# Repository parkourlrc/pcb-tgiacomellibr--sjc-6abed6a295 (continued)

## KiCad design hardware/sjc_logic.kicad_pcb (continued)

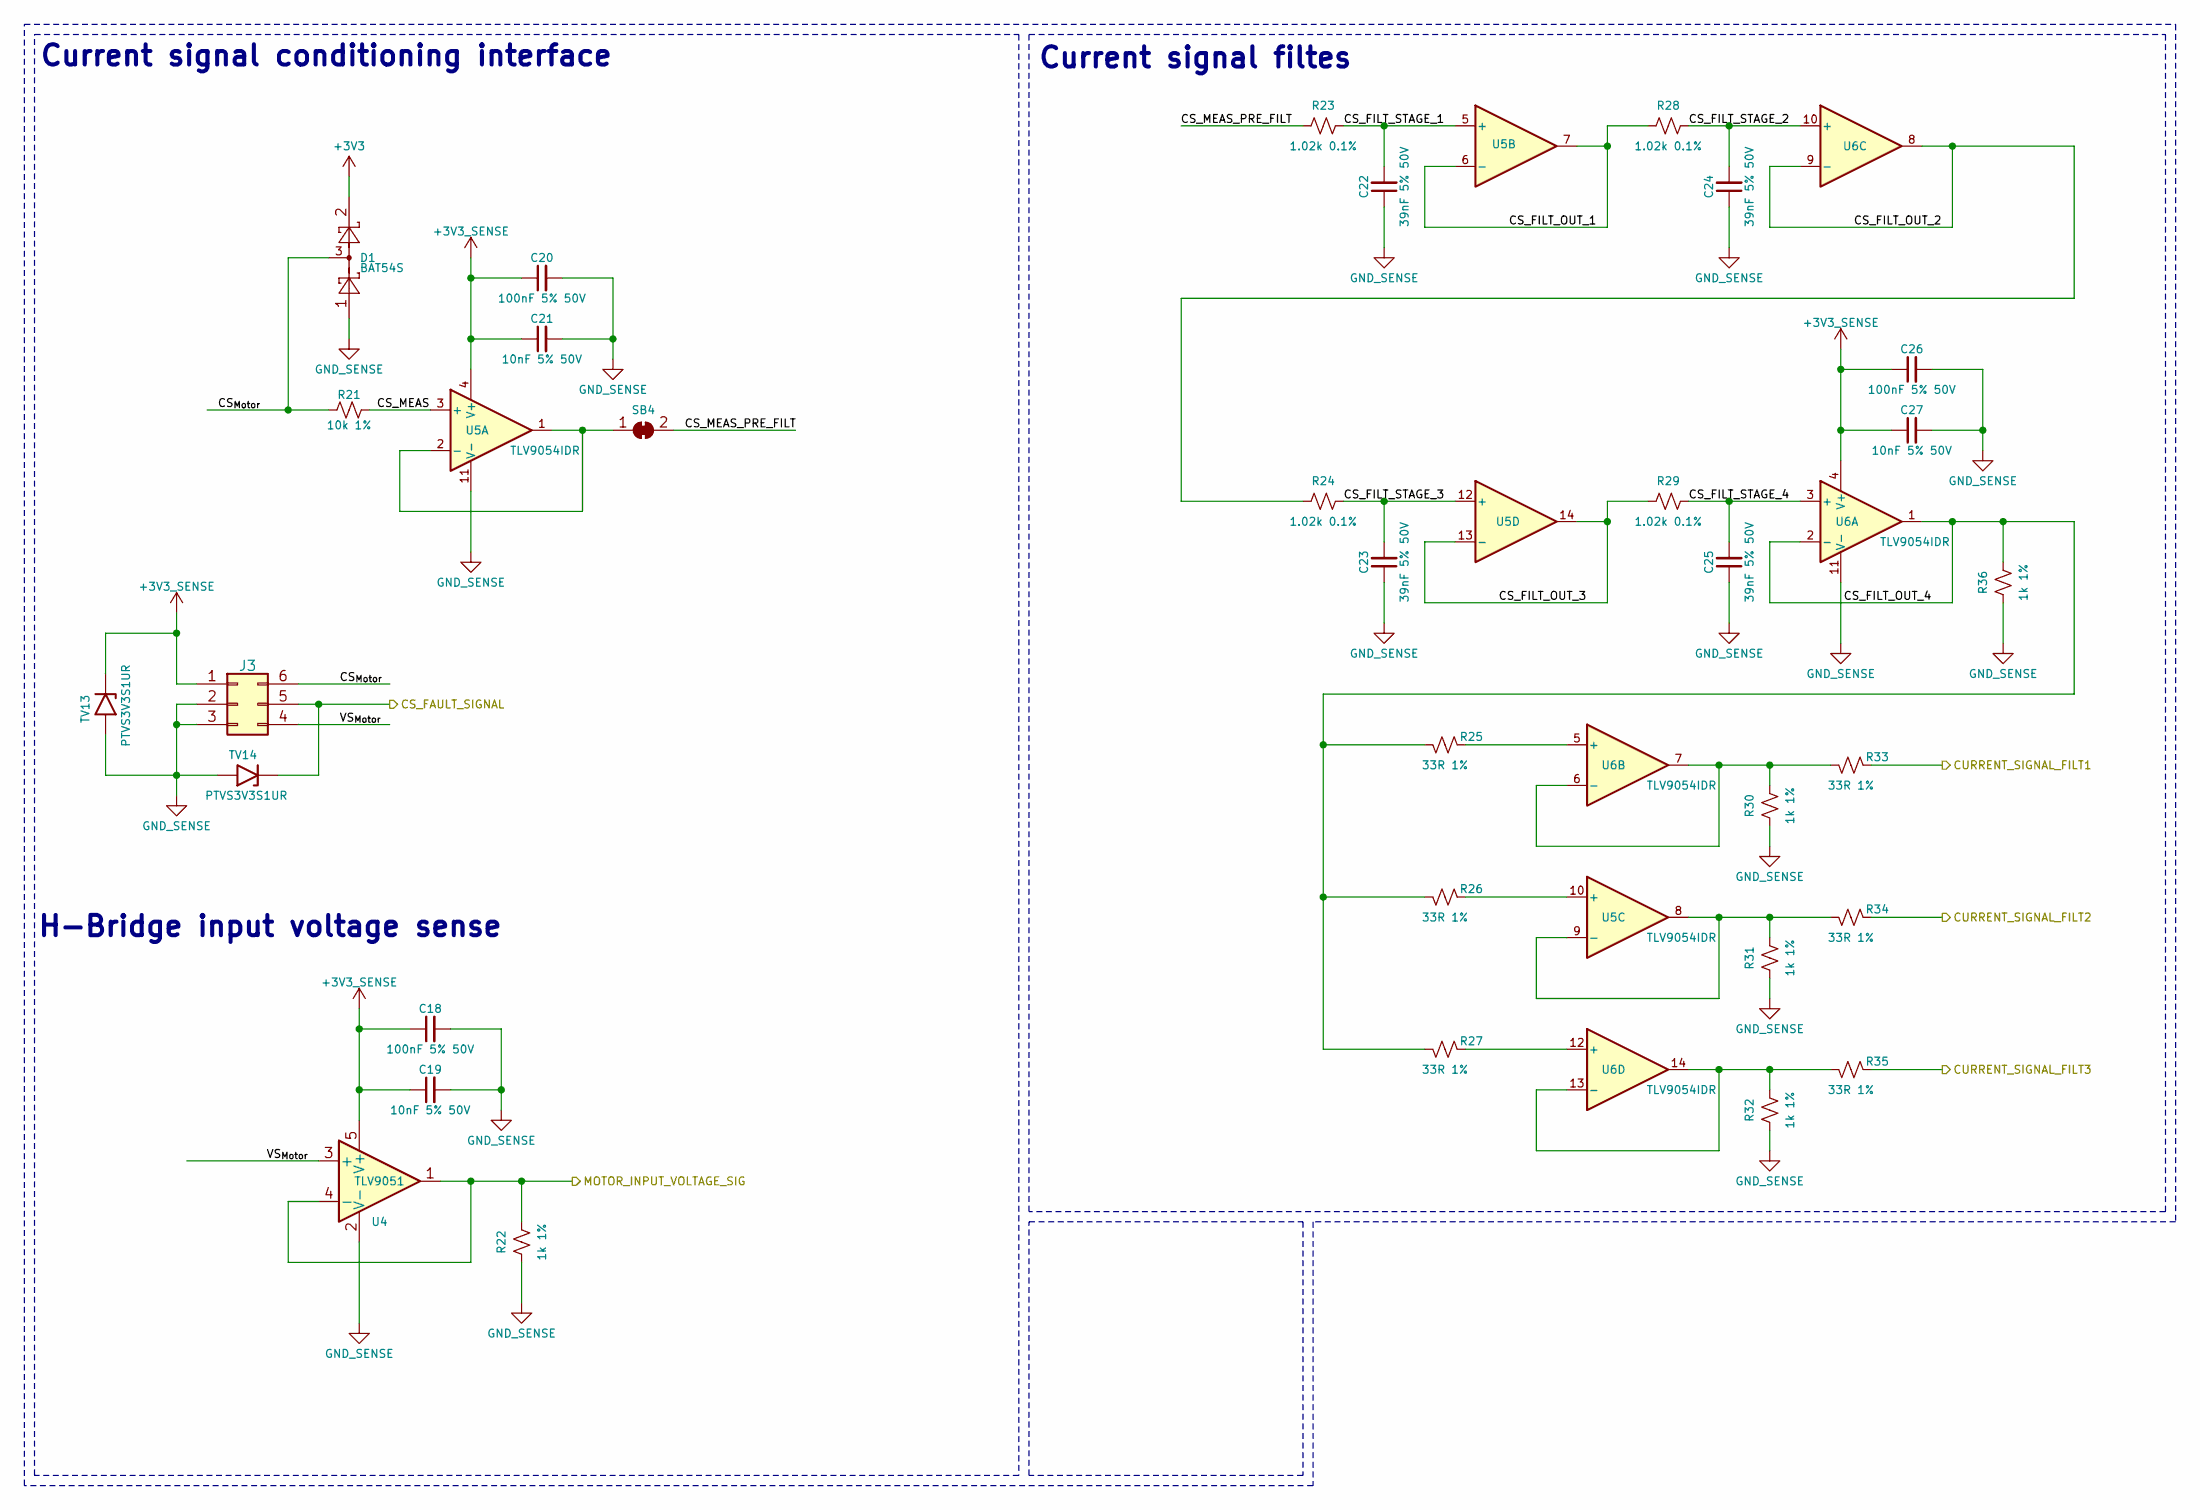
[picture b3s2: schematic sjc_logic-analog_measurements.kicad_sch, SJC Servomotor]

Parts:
C18, C20, C26: 100nF 5% 50V; C_0603_1608Metric; JLCPCB Part # C91183
C19, C21, C27: 10nF 5% 50V; C_0603_1608Metric; JLCPCB Part # C389113
C22, C23, C24, C25: 39nF 5% 50V; C_0603_1608Metric; JLCPCB Part # C519553
D1: BAT54S; SOT-23; JLCPCB Part # C19726
J3: External sensors; PinHeader_2x03_P2.54mm_Vertical
R21: 10k 1%; R_0603_1608Metric; JLCPCB Part # C98220
R22, R30, R31, R32, R36: 1k 1%; R_0603_1608Metric; JLCPCB Part # C22548
R23, R24, R28, R29: 1.02k 0.1%; R_0603_1608Metric; JLCPCB Part # C705819
R25, R26, R27, R33, R34, R35: 33R 1%; R_0603_1608Metric; JLCPCB Part # C108661
SB4: SolderJumper-2_P1.3mm_Bridged2Bar_RoundedPad1.0x1.5mm
TV13, TV14: PTVS3V3S1UR; D_SOD-123; JLCPCB Part # C183521
U4: TLV9051; SOT-23-5; JLCPCB Part # C1849429
U5, U6: TLV9054IDR; SOIC-14_3.9x8.7mm_P1.27mm; JLCPCB Part # C2057745

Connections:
+3V3: D1.2; also elsewhere on the board
+3V3_SENSE: C18.1, C19.1, C20.1, C21.1, C26.1, C27.1, J3.1, TV13.1 (K), U4.5 (V+), U5.4 (V+), U6.4 (V+); also elsewhere on the board
/Analog Measurement/CS_FAULT_SIGNAL: J3.5, TV14.1 (K)
/Analog Measurement/CS_FILT_OUT_1: R28.1, U5.6 (-), U5.7
/Analog Measurement/CS_FILT_OUT_2: R24.1, U6.8, U6.9 (-)
/Analog Measurement/CS_FILT_OUT_3: R29.1, U5.13 (-), U5.14
/Analog Measurement/CS_FILT_OUT_4: R25.2, R26.2, R27.2, R36.2, U6.1, U6.2 (-)
/Analog Measurement/CS_FILT_STAGE_1: C22.2, R23.2, U5.5 (+)
/Analog Measurement/CS_FILT_STAGE_2: C24.2, R28.2, U6.10 (+)
/Analog Measurement/CS_FILT_STAGE_3: C23.2, R24.2, U5.12 (+)
/Analog Measurement/CS_FILT_STAGE_4: C25.2, R29.2, U6.3 (+)
/Analog Measurement/CS_MEAS: R21.2, U5.3 (+)
/Analog Measurement/CS_MEAS_PRE_FILT: R23.1, SB4.2 (B)
/Analog Measurement/CS_{Motor}: D1.3, J3.6, R21.1
/Analog Measurement/CURRENT_SIGNAL_FILT1: R33.1
/Analog Measurement/CURRENT_SIGNAL_FILT2: R34.1
/Analog Measurement/CURRENT_SIGNAL_FILT3: R35.1
/Analog Measurement/MOTOR_INPUT_VOLTAGE_SIG: R22.2, U4.1, U4.4 (-)
/Analog Measurement/VS_{Motor}: J3.4, U4.3 (+)
GND_SENSE: C18.2, C19.2, C20.2, C21.2, C22.1, C23.1, C24.1, C25.1, C26.2, C27.2, D1.1, J3.2, J3.3, R22.1, R30.1, R31.1, R32.1, R36.1, TV13.2 (A), TV14.2 (A), U4.2 (V-), U5.11 (V-), U6.11 (V-); also elsewhere on the board
unnamed: SB4.1 (A), U5.1, U5.2 (-)
unnamed: R26.1, U5.10 (+)
unnamed: R31.2, R34.2, U5.8, U5.9 (-)
unnamed: R25.1, U6.5 (+)
unnamed: R30.2, R33.2, U6.6 (-), U6.7
unnamed: R27.1, U6.12 (+)
unnamed: R32.2, R35.2, U6.13 (-), U6.14

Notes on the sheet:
Current signal conditioning interface
H-Bridge input voltage sense
Current signal filtes

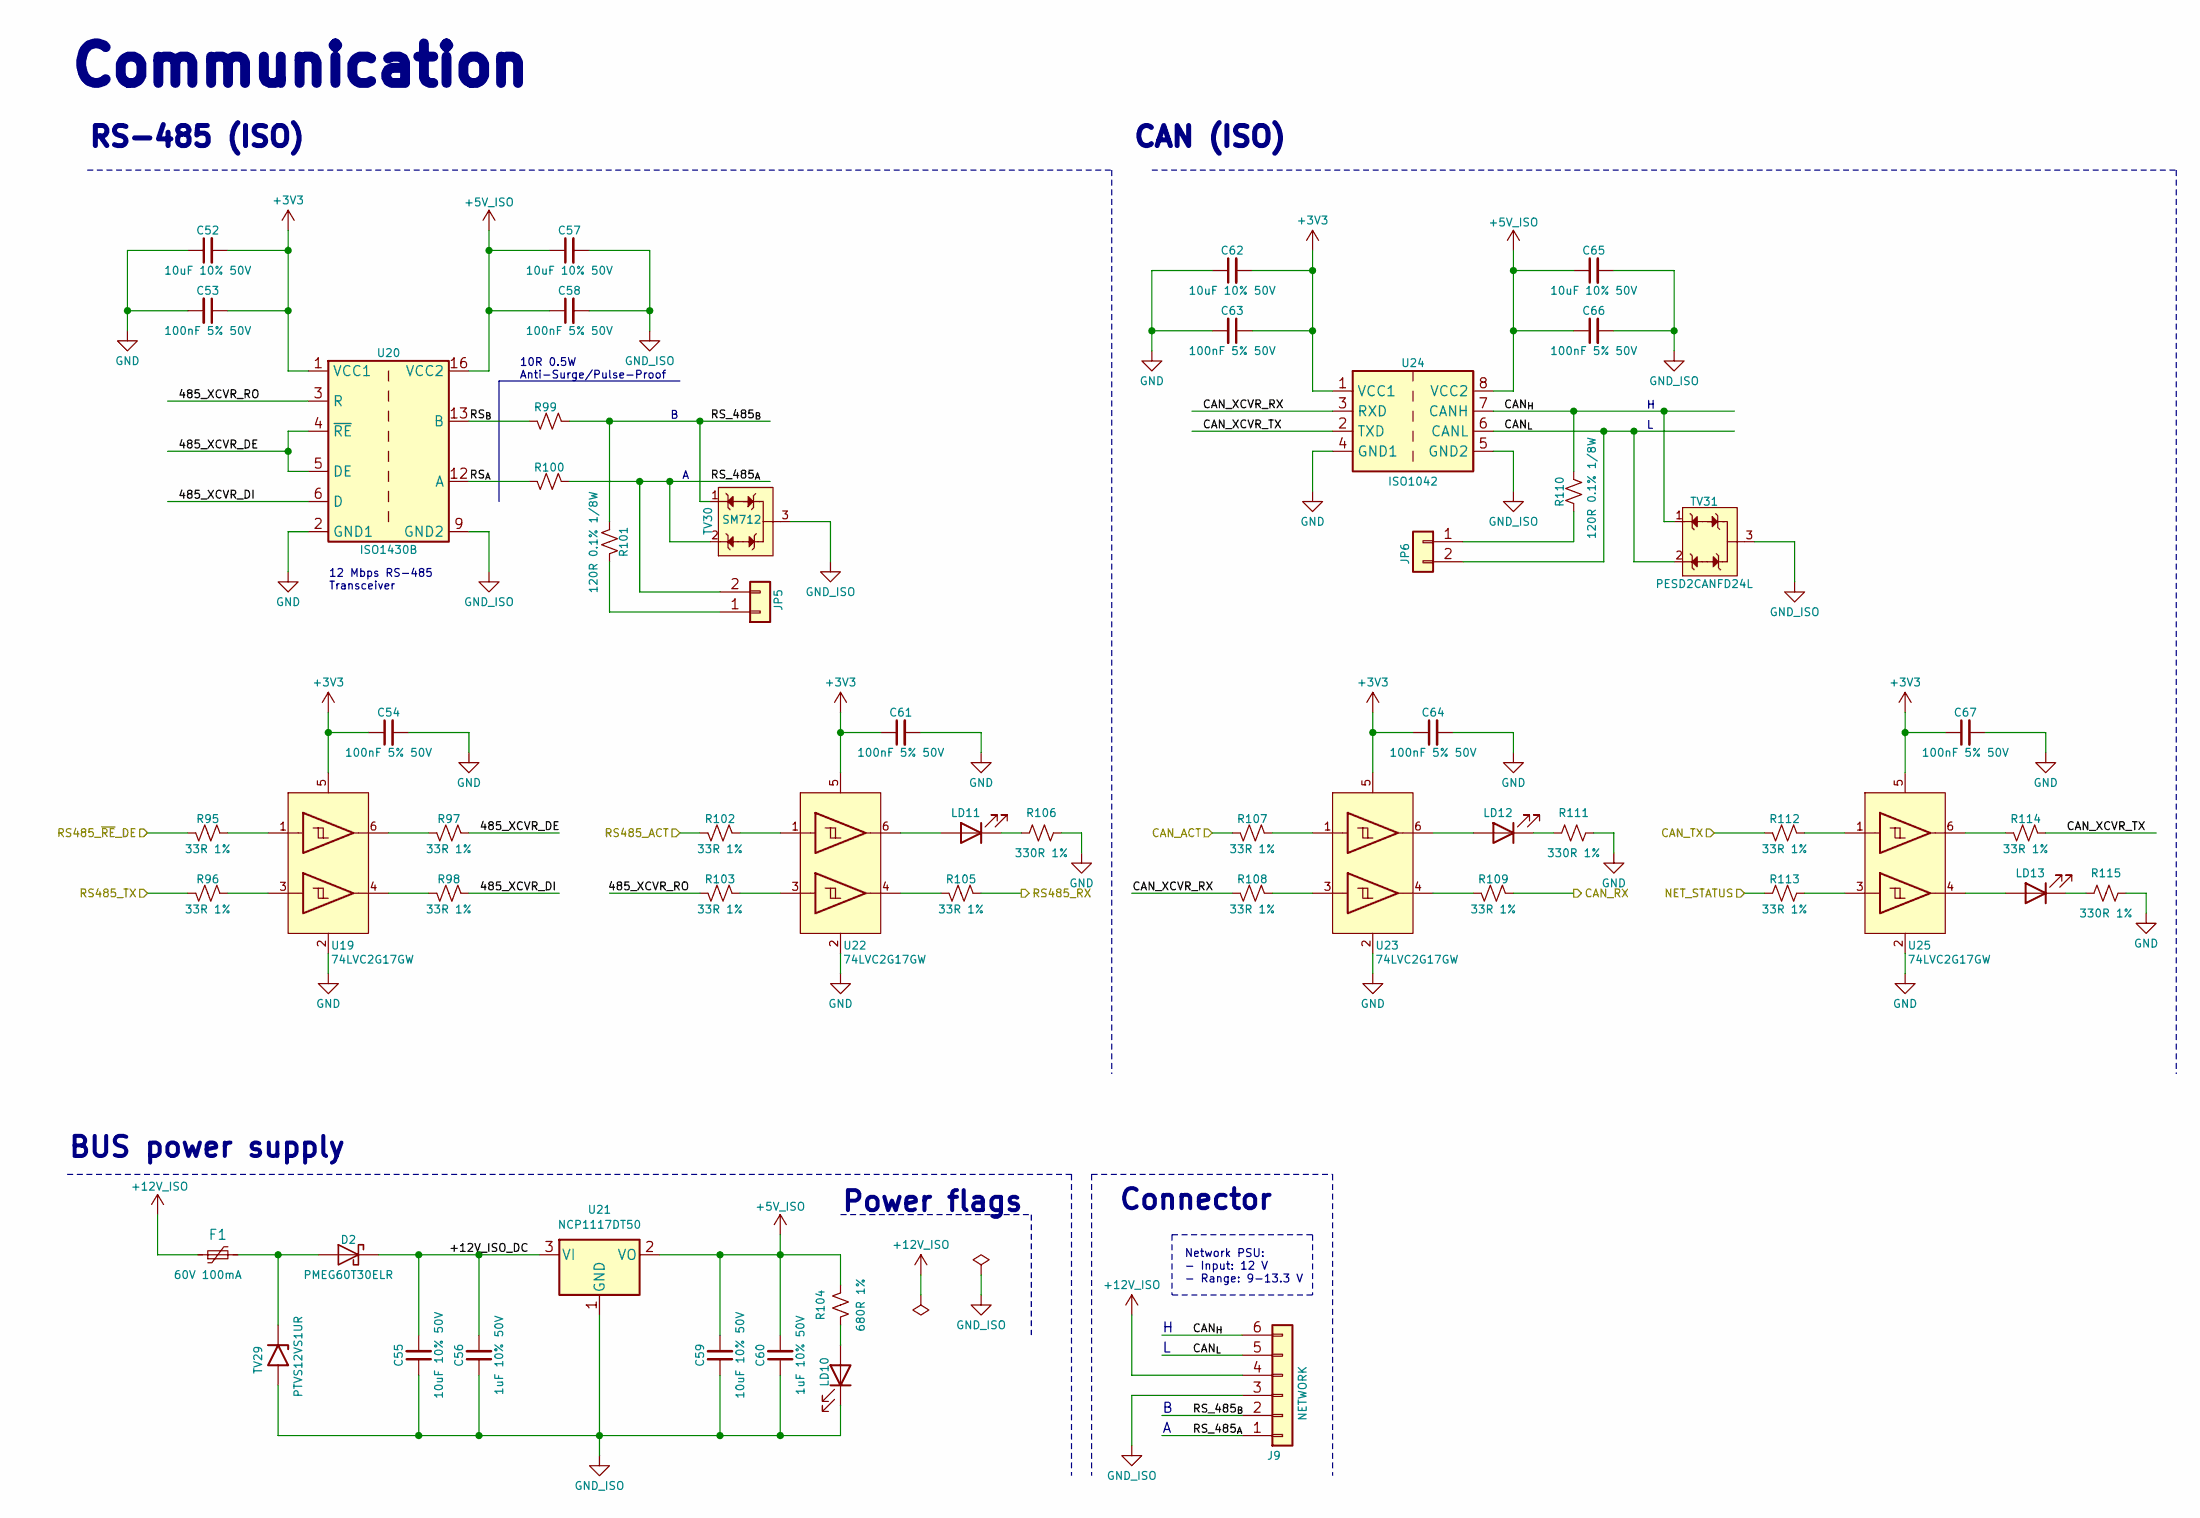
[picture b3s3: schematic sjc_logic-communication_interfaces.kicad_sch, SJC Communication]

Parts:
C52, C55, C57, C59, C62, C65: 10uF 10% 50V; C_1206_3216Metric; JLCPCB Part # C13585
C53, C54, C58, C61, C63, C64, C66, C67: 100nF 5% 50V; C_0603_1608Metric; JLCPCB Part # C91183
C56, C60: 1uF 10% 50V; C_1206_3216Metric; JLCPCB Part # C1848
D2: PMEG60T30ELR; D_SOD-123F; JLCPCB Part # C2938304
F1: 60V 100mA; Fuse_1206_3216Metric; JLCPCB Part # C2153714
J9: NETWORK; TerminalBlock_Phoenix_MKDS-3-6-5.08_1x06_P5.08mm_Horizontal; JLCPCB Part # C2915642
JP5, JP6: RS-485 TERM; PinHeader_1x02_P2.54mm_Vertical; JLCPCB Part # C225477
LD10, LD11, LD12, LD13: 1.8V @ 5mA; LED_0603_1608Metric_Pad1.05x0.95mm_HandSolder; JLCPCB Part # C165982
R95, R96, R97, R98, R102, R103, R105, R107, R108, R109, R112, R113, R114: 33R 1%; R_0603_1608Metric; JLCPCB Part # C108661
R99, R100: 10R 5% 1/2W; R_0805_2012Metric_Pad1.20x1.40mm_HandSolder; JLCPCB Part # C966152
R101, R110: 120R 0.1% 1/8W; R_0805_2012Metric_Pad1.20x1.40mm_HandSolder; JLCPCB Part # C2828708
R104: 680R 1%; R_0603_1608Metric; JLCPCB Part # C966615
R106, R111, R115: 330R 1%; R_0603_1608Metric; JLCPCB Part # C144102
TV29: PTVS12VS1UR; D_SOD-123; JLCPCB Part # C456115
TV30: SM712; SOT-23-3; JLCPCB Part # C293966
TV31: PESD2CANFD24L; SOT-23W_Handsoldering; LCSC Part # C3711787
U19, U22, U23, U25: 74LVC2G17GW; SOT-363_SC-70-6; JLCPCB Part # C80500
U20: ISO1430B; SOIC-16W_7.5x10.3mm_P1.27mm; JLCPCB Part # C2869747
U21: NCP1117DT50; TO-252-2; JLCPCB Part # C152470
U24: ISO1042; SOIC-8_7.5x5.85mm_P1.27mm; JLCPCB Part # C2671714

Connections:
+3V3: C52.2, C53.1, C54.1, C61.1, C62.2, C63.1, C64.1, C67.1, U19.5 (VCC), U20.1 (VCC1), U22.5 (VCC), U23.5 (VCC), U24.1 (VCC1), U25.5 (VCC); also elsewhere on the board
+5V_ISO: C57.1, C58.1, C59.2, C60.2, C65.1, C66.1, R104.1, U20.16 (VCC2), U21.2 (VO), U24.8 (VCC2)
+12V_ISO: F1.1, J9.4
/Communication Interfaces/485_XCVR_DE: R97.1, U20.4 (~RE), U20.5 (DE)
/Communication Interfaces/485_XCVR_DI: R98.1, U20.6 (D)
/Communication Interfaces/485_XCVR_RO: R103.2, U20.3 (R)
/Communication Interfaces/+12V_ISO_DC: C55.2, C56.2, D2.1 (K), U21.3 (VI)
/Communication Interfaces/CAN_ACT: R107.2; also elsewhere on the board
/Communication Interfaces/CAN_RX: R109.1; also elsewhere on the board
/Communication Interfaces/CAN_TX: R112.2; also elsewhere on the board
/Communication Interfaces/CAN_XCVR_RX: R108.2, U24.3 (RXD)
/Communication Interfaces/CAN_XCVR_TX: R114.1, U24.2 (TXD)
/Communication Interfaces/CAN_{H}: J9.6, R110.1, TV31.1 (K1), U24.7 (CANH)
/Communication Interfaces/CAN_{L}: J9.5, JP6.2, TV31.2 (K2), U24.6 (CANL)
/Communication Interfaces/NET_STATUS: R113.1; also elsewhere on the board
/Communication Interfaces/RS485_ACT: R102.2; also elsewhere on the board
/Communication Interfaces/RS485_RX: R105.1; also elsewhere on the board
/Communication Interfaces/RS485_TX: R96.2; also elsewhere on the board
/Communication Interfaces/RS485_~RE_DE: R95.2; also elsewhere on the board
/Communication Interfaces/RS_485_{A}: J9.1, JP5.2, R100.1, TV30.2
/Communication Interfaces/RS_485_{B}: J9.2, R99.1, R101.1, TV30.1
/Communication Interfaces/RS_{A}: R100.2, U20.12 (A)
/Communication Interfaces/RS_{B}: R99.2, U20.13 (B)
GND: C52.1, C53.2, C54.2, C61.2, C62.1, C63.2, C64.2, C67.2, R106.2, R111.2, R115.2, U19.2 (GND), U20.2 (GND1), U20.8 (GND1), U22.2 (GND), U23.2 (GND), U24.4 (GND1), U25.2 (GND); also elsewhere on the board
GND_ISO: C55.1, C56.1, C57.2, C58.2, C59.1, C60.1, C65.2, C66.2, J9.3, LD10.1 (K), TV29.2 (A), TV30.3, TV31.3 (CC), U20.9 (GND2), U20.15 (GND2), U21.1 (GND), U24.5 (GND2)
unnamed: D2.2 (A), F1.2, TV29.1 (K)
unnamed: JP5.1, R101.2
unnamed: JP6.1, R110.2
unnamed: LD10.2 (A), R104.2
unnamed: LD11.2 (A), U22.6 (1Y)
unnamed: LD11.1 (K), R106.1
unnamed: LD12.2 (A), U23.6 (1Y)
unnamed: LD12.1 (K), R111.1
unnamed: LD13.2 (A), U25.4 (2Y)
unnamed: LD13.1 (K), R115.1
unnamed: R95.1, U19.1 (1A)
unnamed: R97.2, U19.6 (1Y)
unnamed: R96.1, U19.3 (2A)
unnamed: R98.2, U19.4 (2Y)
unnamed: R102.1, U22.1 (1A)
unnamed: R103.1, U22.3 (2A)
unnamed: R105.2, U22.4 (2Y)
unnamed: R107.1, U23.1 (1A)
unnamed: R108.1, U23.3 (2A)
unnamed: R109.2, U23.4 (2Y)
unnamed: R112.1, U25.1 (1A)
unnamed: R114.2, U25.6 (1Y)
unnamed: R113.2, U25.3 (2A)

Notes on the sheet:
RS-485 (ISO)
10R 0.5W Anti-Surge/Pulse-Proof
Power flags
CAN (ISO)
12 Mbps RS-485 Transceiver
BUS power supply
Connector
Communication
Network PSU: - Input: 12 V - Range: 9-13.3 V

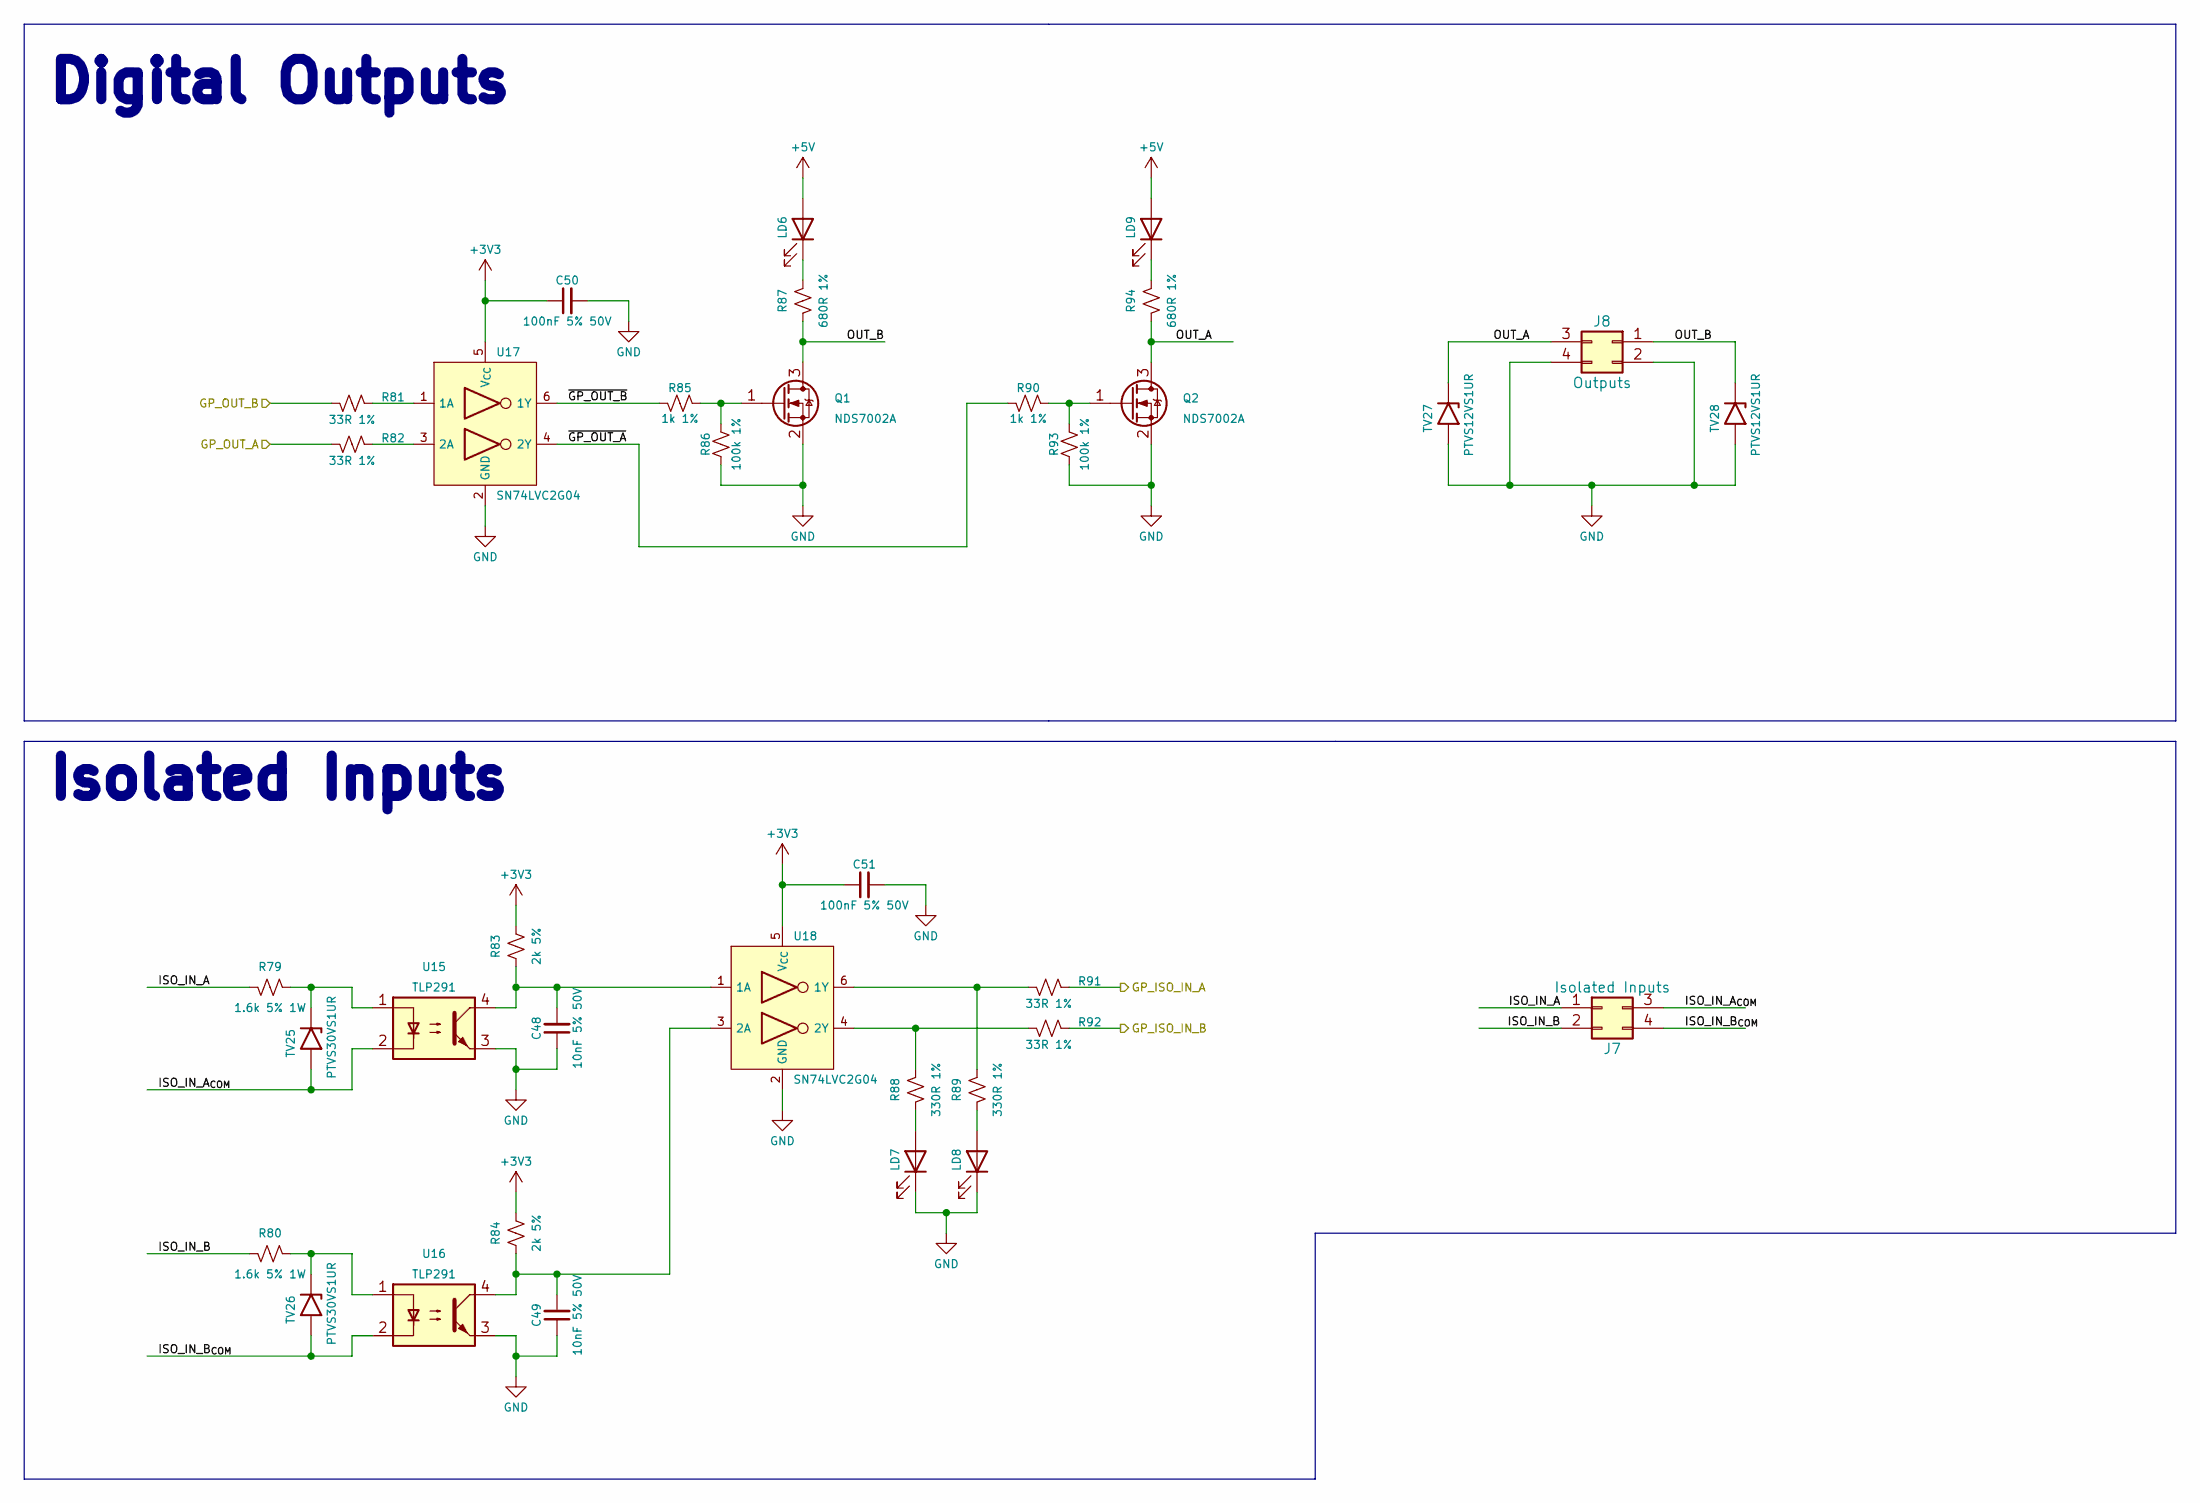
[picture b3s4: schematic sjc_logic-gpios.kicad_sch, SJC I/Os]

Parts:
C48, C49: 10nF 5% 50V; C_0603_1608Metric; JLCPCB Part # C389113
C50, C51: 100nF 5% 50V; C_0603_1608Metric; JLCPCB Part # C91183
J7: Isolated Inputs; Molex_Micro-Fit_3.0_43045-0412_2x02_P3.00mm_Vertical
J8: Outputs; Molex_Micro-Fit_3.0_43045-0412_2x02_P3.00mm_Vertical
LD6, LD7, LD8, LD9: 1.8V @ 5mA; LED_0603_1608Metric_Pad1.05x0.95mm_HandSolder; JLCPCB Part # C165982
Q1, Q2: NDS7002A; SOT-23; JLCPCB Part # C74715
R79, R80: 1.6k 5% 1W; R_2512_6332Metric_Pad1.40x3.35mm_HandSolder; JLCPCB Part # C453392
R81, R82, R91, R92: 33R 1%; R_0603_1608Metric; JLCPCB Part # C108661
R83, R84: 2k 5%; R_0603_1608Metric; JLCPCB Part # C103396
R85, R90: 1k 1%; R_0603_1608Metric; JLCPCB Part # C22548
R86, R93: 100k 1%; R_0603_1608Metric; JLCPCB Part # C14675
R87, R94: 680R 1%; R_0603_1608Metric; JLCPCB Part # C966615
R88, R89: 330R 1%; R_0603_1608Metric; JLCPCB Part # C144102
TV25, TV26: PTVS30VS1UR; D_SOD-123; JLCPCB Part # C553410
TV27, TV28: PTVS12VS1UR; D_SOD-123; JLCPCB Part # C456115
U15, U16: TLP291; SOP-4_4.4x2.6mm_P1.27mm; JLCPCB Part # C55144
U17, U18: SN74LVC2G04; SOT-23-6_Handsoldering; JLCPCB Part # C10428

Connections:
+3V3: C50.1, C51.1, R83.2, R84.2, U17.5 (V_{CC}), U18.5 (V_{CC}); also elsewhere on the board
+5V: LD6.2 (A), LD9.2 (A); also elsewhere on the board
/Control/GP_ISO_IN_A: R91.1
/Control/GP_ISO_IN_B: R92.1
/Control/GP_OUT_A: R82.2; also elsewhere on the board
/Control/GP_OUT_B: R81.2; also elsewhere on the board
/GPIOs/ISO_IN_A: J7.1, R79.2
/GPIOs/ISO_IN_A_{COM}: J7.3, TV25.2 (A), U15.2
/GPIOs/ISO_IN_B: J7.2, R80.2
/GPIOs/ISO_IN_B_{COM}: J7.4, TV26.2 (A), U16.2
/GPIOs/OUT_A: J8.3, Q2.3 (D), R94.2, TV27.1 (K)
/GPIOs/OUT_B: J8.1, Q1.3 (D), R87.2, TV28.1 (K)
/GPIOs/~GP_OUT_A: R90.2, U17.4 (2Y)
/GPIOs/~GP_OUT_B: R85.2, U17.6 (1Y)
GND: C48.1, C49.1, C50.2, C51.2, J8.2, J8.4, LD7.1 (K), LD8.1 (K), Q1.2 (S), Q2.2 (S), R86.1, R93.1, TV27.2 (A), TV28.2 (A), U15.3, U16.3, U17.2 (GND), U18.2 (GND); also elsewhere on the board
unnamed: LD6.1 (K), R87.1
unnamed: LD7.2 (A), R88.2
unnamed: LD8.2 (A), R89.2
unnamed: LD9.1 (K), R94.1
unnamed: Q1.1 (G), R85.1, R86.2
unnamed: Q2.1 (G), R90.1, R93.2
unnamed: R79.1, TV25.1 (K), U15.1
unnamed: R80.1, TV26.1 (K), U16.1
unnamed: R81.1, U17.1 (1A)
unnamed: R82.1, U17.3 (2A)
unnamed: C48.2, R83.1, U15.4, U18.1 (1A)
unnamed: R89.1, R91.2, U18.6 (1Y)
unnamed: C49.2, R84.1, U16.4, U18.3 (2A)
unnamed: R88.1, R92.2, U18.4 (2Y)

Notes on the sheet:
Isolated Inputs
Digital Outputs

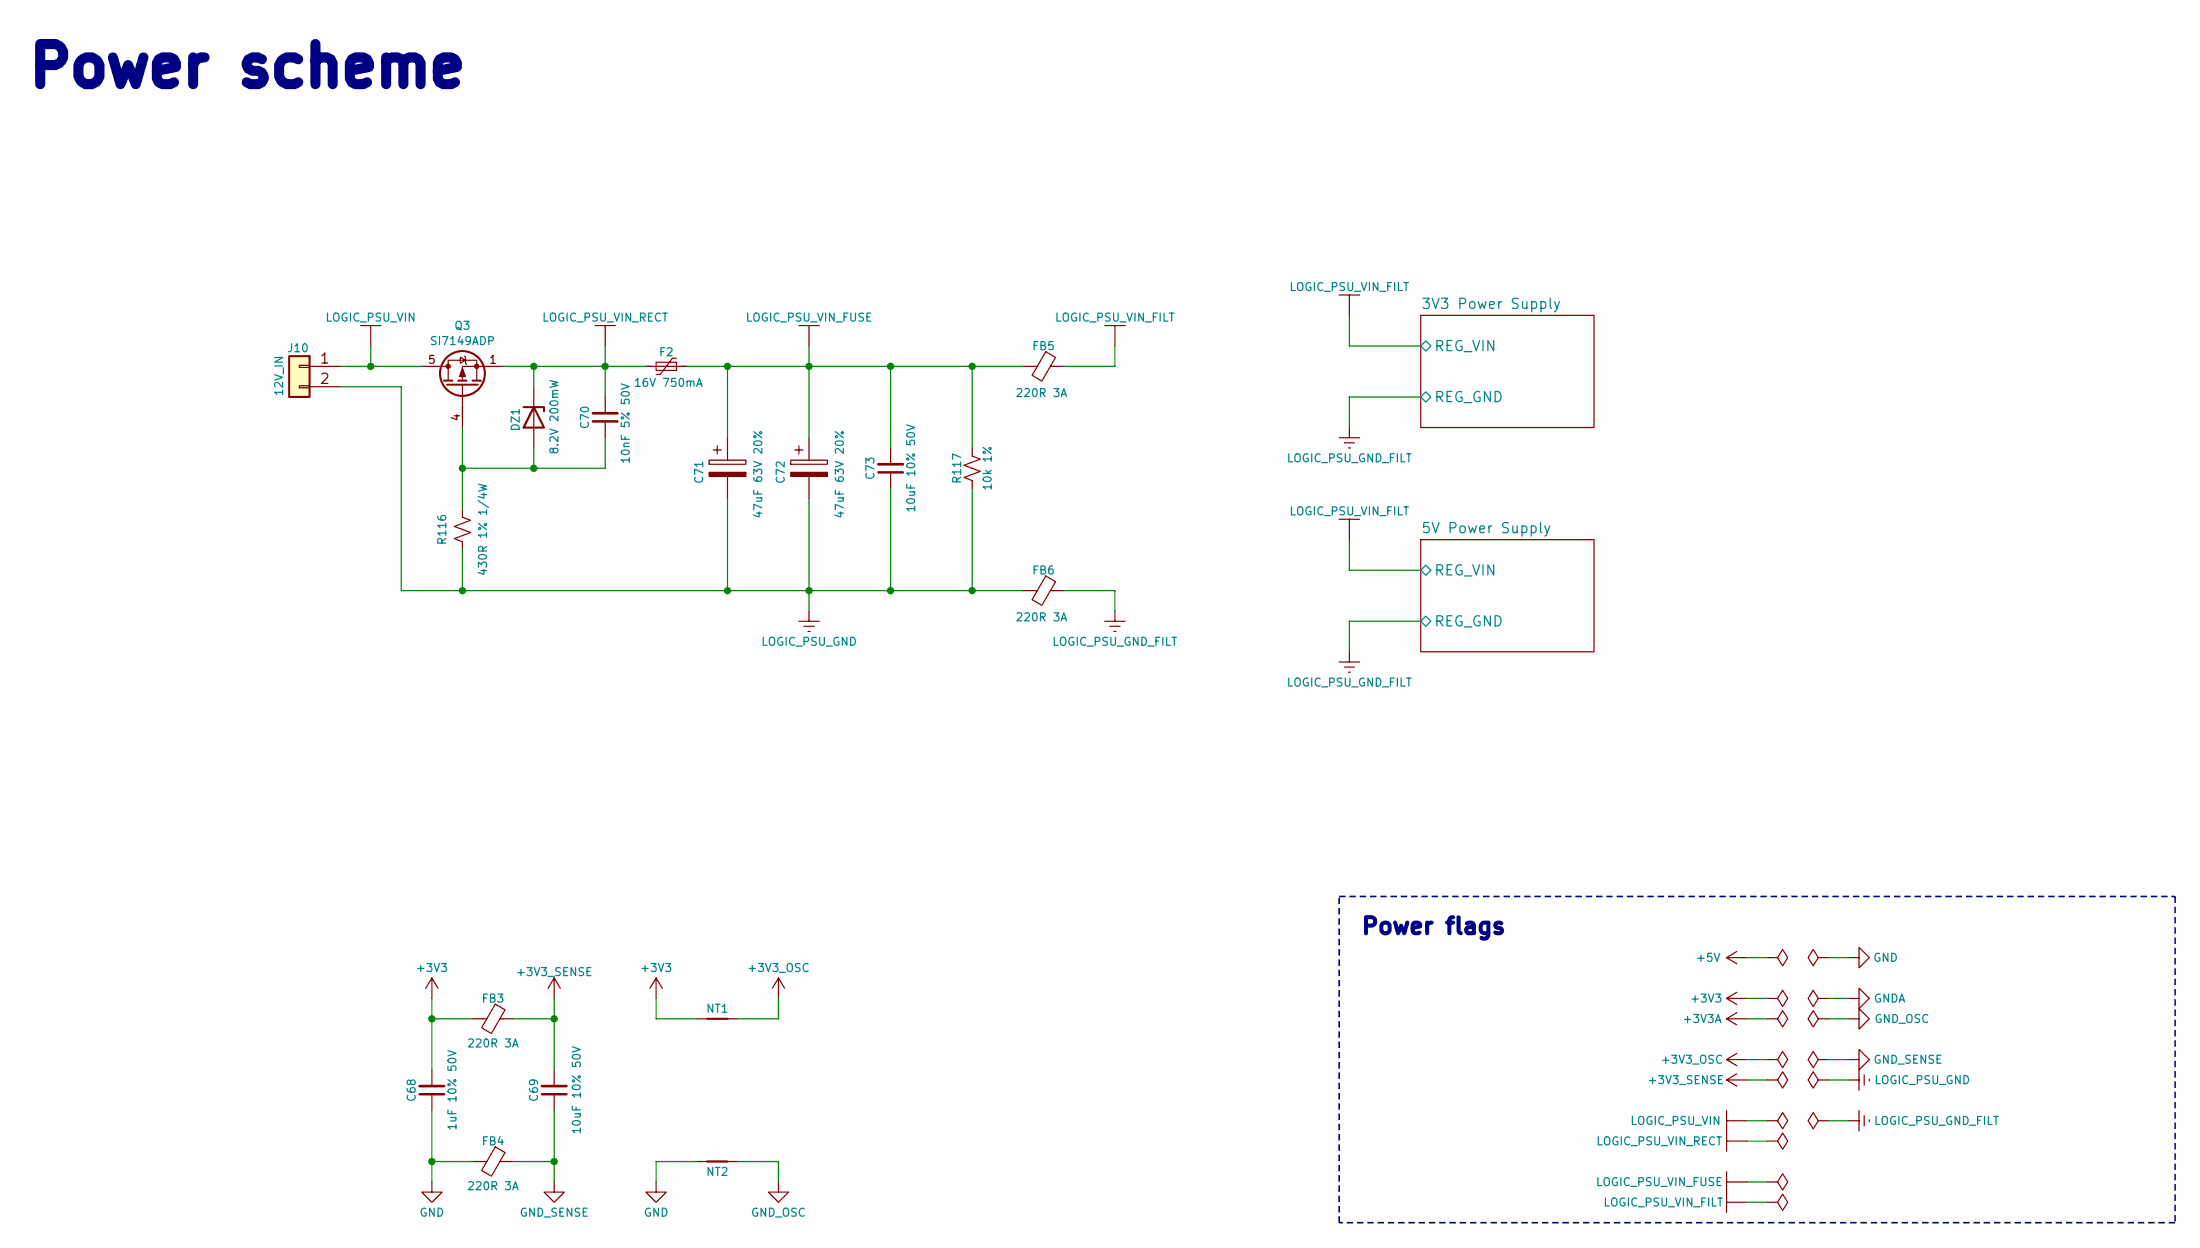
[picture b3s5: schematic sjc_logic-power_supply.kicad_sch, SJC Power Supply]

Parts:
C68: 1uF 10% 50V; C_1206_3216Metric; JLCPCB Part # C1848
C69, C73: 10uF 10% 50V; C_1206_3216Metric; JLCPCB Part # C13585
C70: 10nF 5% 50V; C_0603_1608Metric; JLCPCB Part # C389113
C71, C72: 47uF 63V 20%; CP_Elec_8x10.5; JLCPCB Part # C116428
DZ1: 8.2V 200mW; D_SOD-323; JLCPCB Part # C264108
F2: 16V 750mA; Fuse_1206_3216Metric_Pad1.42x1.75mm_HandSolder; JLCPCB Part # C371166
FB3, FB4, FB5, FB6: 220R 3A; L_0805_2012Metric_Pad1.05x1.20mm_HandSolder; JLCPCB Part # C76818
J10: 12V_IN; TerminalBlock_Phoenix_MKDS-3-2-5.08_1x02_P5.08mm_Horizontal; JLCPCB Part # C2915639
NT1, NT2: NetTie-2_SMD_Pad0.5mm
Q3: SI7149ADP; PowerPAK_SO-8_Single; JLCPCB Part # C554002
R116: 430R 1% 1/4W; R_1206_3216Metric; JLCPCB Part # C17965
R117: 10k 1%; R_0603_1608Metric; JLCPCB Part # C98220

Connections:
+3V3: C68.2, FB3.2, NT1.1; also elsewhere on the board
+3V3_OSC: NT1.2; also elsewhere on the board
+3V3_SENSE: C69.2, FB3.1; also elsewhere on the board
GND: C68.1, FB4.2, NT2.2; also elsewhere on the board
GND_OSC: NT2.1; also elsewhere on the board
GND_SENSE: C69.1, FB4.1; also elsewhere on the board
LOGIC_PSU_GND: C71.2, C72.2, C73.1, FB6.2, J10.2, R116.1, R117.1
LOGIC_PSU_GND_FILT: FB6.1; also elsewhere on the board
LOGIC_PSU_VIN: J10.1, Q3.5 (D)
LOGIC_PSU_VIN_FILT: FB5.1; also elsewhere on the board
LOGIC_PSU_VIN_FUSE: C71.1, C72.1, C73.2, F2.1, FB5.2, R117.2
LOGIC_PSU_VIN_RECT: C70.2, DZ1.1 (K), F2.2, Q3.1 (S), Q3.2 (S), Q3.3 (S)
unnamed: C70.1, DZ1.2 (A), Q3.4 (G), R116.2

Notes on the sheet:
Power scheme
Power flags
